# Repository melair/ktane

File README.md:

# Keep Talking and Nobody Explodes - Physical Version

## Version Two

This is version two of my Keep Talking and Nobody Explodes physical bomb, you may refer to the `version-one` branch if you wish to see the first version progress.

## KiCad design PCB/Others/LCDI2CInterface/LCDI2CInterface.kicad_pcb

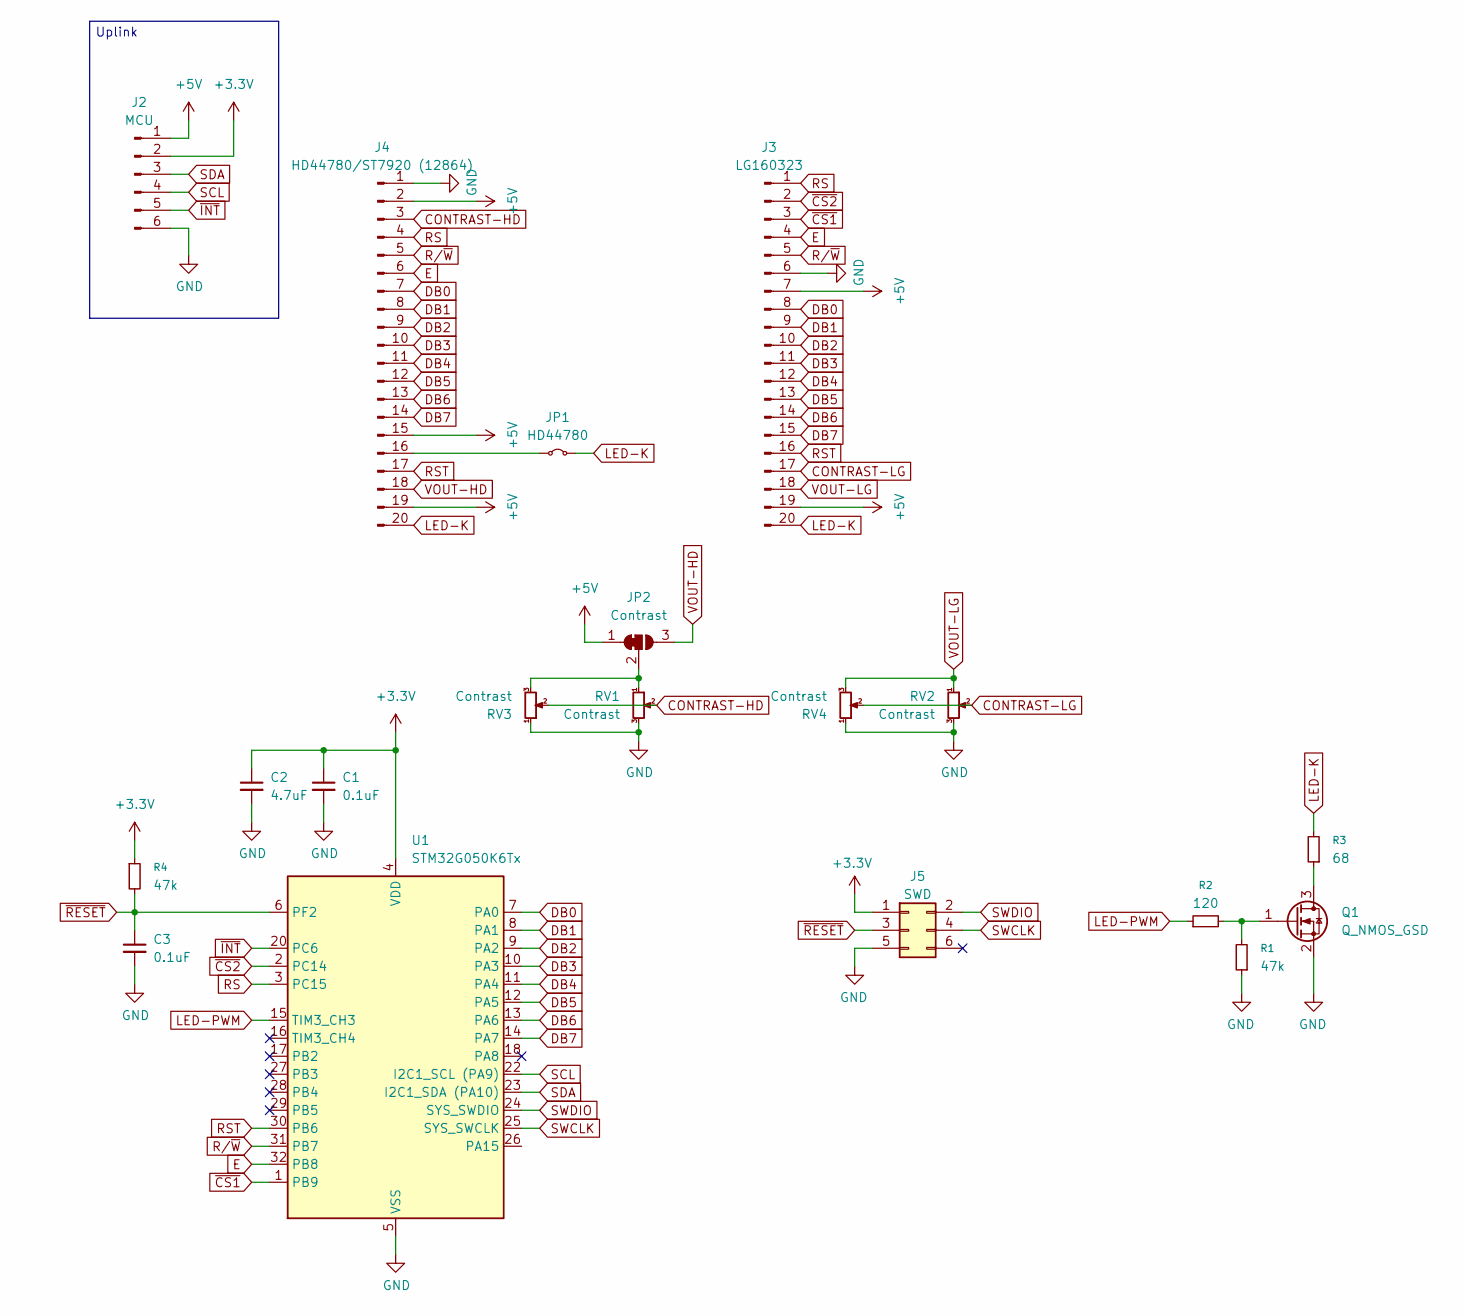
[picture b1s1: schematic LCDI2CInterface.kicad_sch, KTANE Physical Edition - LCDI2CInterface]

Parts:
C1, C3: 0.1uF; C_0603_1608Metric
C2: 4.7uF; C_0603_1608Metric
J2: MCU; PinHeader_1x06_P2.54mm_Horizontal
J3: LG160323; PinHeader_1x20_P2.54mm_Vertical
J4: HD44780/ST7920 (12864); PinHeader_1x20_P2.54mm_Vertical
J5: SWD; Tag-Connect_TC2030-IDC-NL_2x03_P1.27mm_Vertical; DIGIKEY NONE
JP1: HD44780; SolderJumper-2_P1.3mm_Bridged_RoundedPad1.0x1.5mm
JP2: Contrast; SolderJumper-3_P1.3mm_Bridged12_RoundedPad1.0x1.5mm
Q1: Q_NMOS_GSD; SOT-23
R1, R4: 47k; R_0603_1608Metric
R2: 120; R_0603_1608Metric
R3: 68; R_0603_1608Metric
RV1, RV2, RV3, RV4: Contrast; Potentiometer_Bourns_TC33X_Vertical; DIGIKEY TC33X-103ECT-ND
U1: STM32G050K6Tx; LQFP-32_7x7mm_P0.8mm

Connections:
+3.3V: C1.1, C2.1, J2.2, J5.1, R4.1, U1.4 (VDD)
+5V: J2.1, J3.7, J3.19, J4.2, J4.15, J4.19, JP2.1 (A)
CONTRAST-HD: J4.3, RV1.2, RV3.2
CONTRAST-LG: J3.17, RV2.2, RV4.2
DB0: J3.8, J4.7, U1.7 (PA0)
DB1: J3.9, J4.8, U1.8 (PA1)
DB2: J3.10, J4.9, U1.9 (PA2)
DB3: J3.11, J4.10, U1.10 (PA3)
DB4: J3.12, J4.11, U1.11 (PA4)
DB5: J3.13, J4.12, U1.12 (PA5)
DB6: J3.14, J4.13, U1.13 (PA6)
DB7: J3.15, J4.14, U1.14 (PA7)
E: J3.4, J4.6, U1.32 (PB8)
GND: C1.2, C2.2, C3.2, J2.6, J3.6, J4.1, J5.5, Q1.2 (S), R1.1, RV1.3, RV2.3, RV3.1, RV4.1, U1.5 (VSS)
LED-K: J3.20, J4.20, JP1.2 (B), R3.2
LED-PWM: R2.1, U1.15 (TIM3_CH3)
unnamed: J4.16, JP1.1 (A)
unnamed: JP2.2 (C), RV1.1, RV3.3
unnamed: Q1.3 (D), R3.1
unnamed: Q1.1 (G), R1.2, R2.2
RS: J3.1, J4.4, U1.3 (PC15)
RST: J3.16, J4.17, U1.30 (PB6)
R/~W: J3.5, J4.5, U1.31 (PB7)
SCL: J2.4, U1.22 (I2C1_SCL (PA9))
SDA: J2.3, U1.23 (I2C1_SDA (PA10))
SWCLK: J5.4, U1.25 (SYS_SWCLK)
SWDIO: J5.2, U1.24 (SYS_SWDIO)
VOUT-HD: J4.18, JP2.3 (B)
VOUT-LG: J3.18, RV2.1, RV4.3
~CS1: J3.3, U1.1 (PB9)
~CS2: J3.2, U1.2 (PC14)
~INT: J2.5, U1.20 (PC6)
~RESET: C3.1, J5.3, R4.2, U1.6 (PF2)

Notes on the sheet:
Uplink

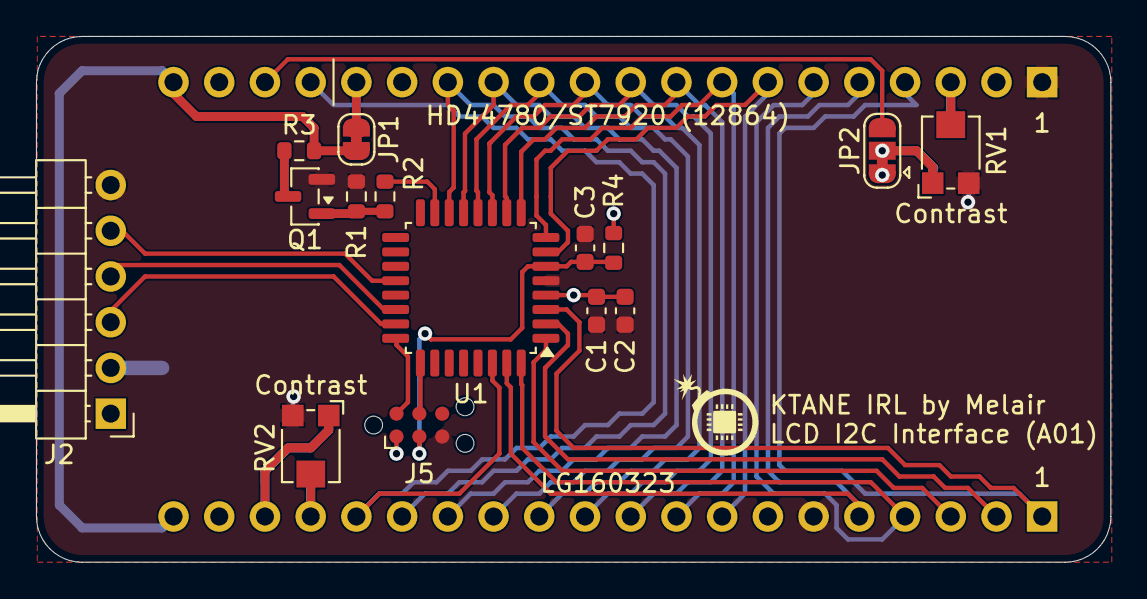
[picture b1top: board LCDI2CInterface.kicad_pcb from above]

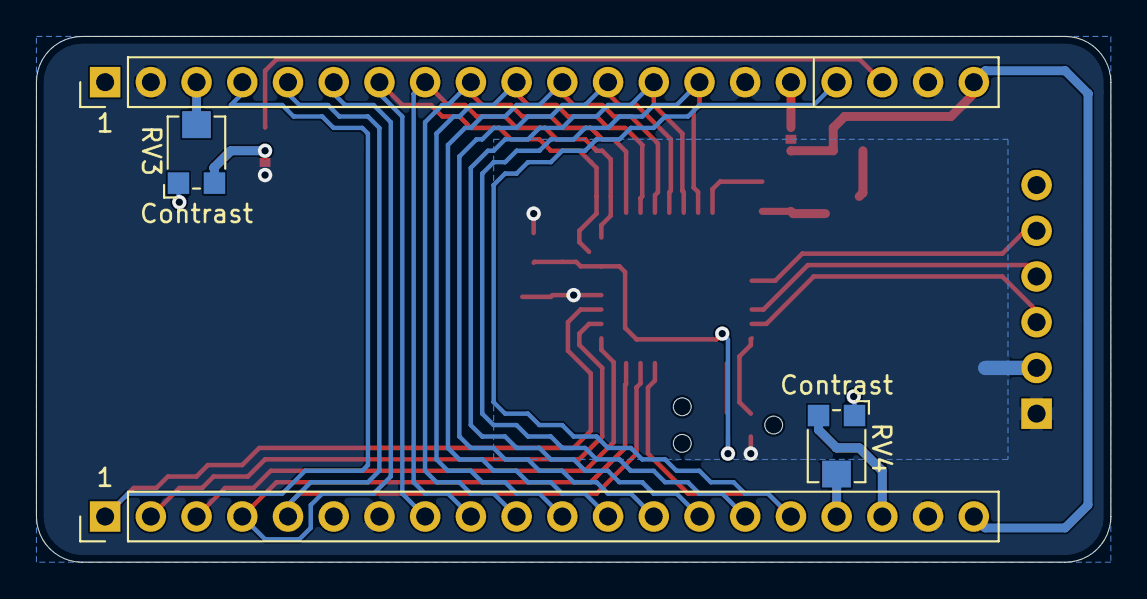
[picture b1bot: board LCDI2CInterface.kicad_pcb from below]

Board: 2 copper layers, 59.7 x 29.2 mm, 19 parts (4 on the bottom side), 33 nets.

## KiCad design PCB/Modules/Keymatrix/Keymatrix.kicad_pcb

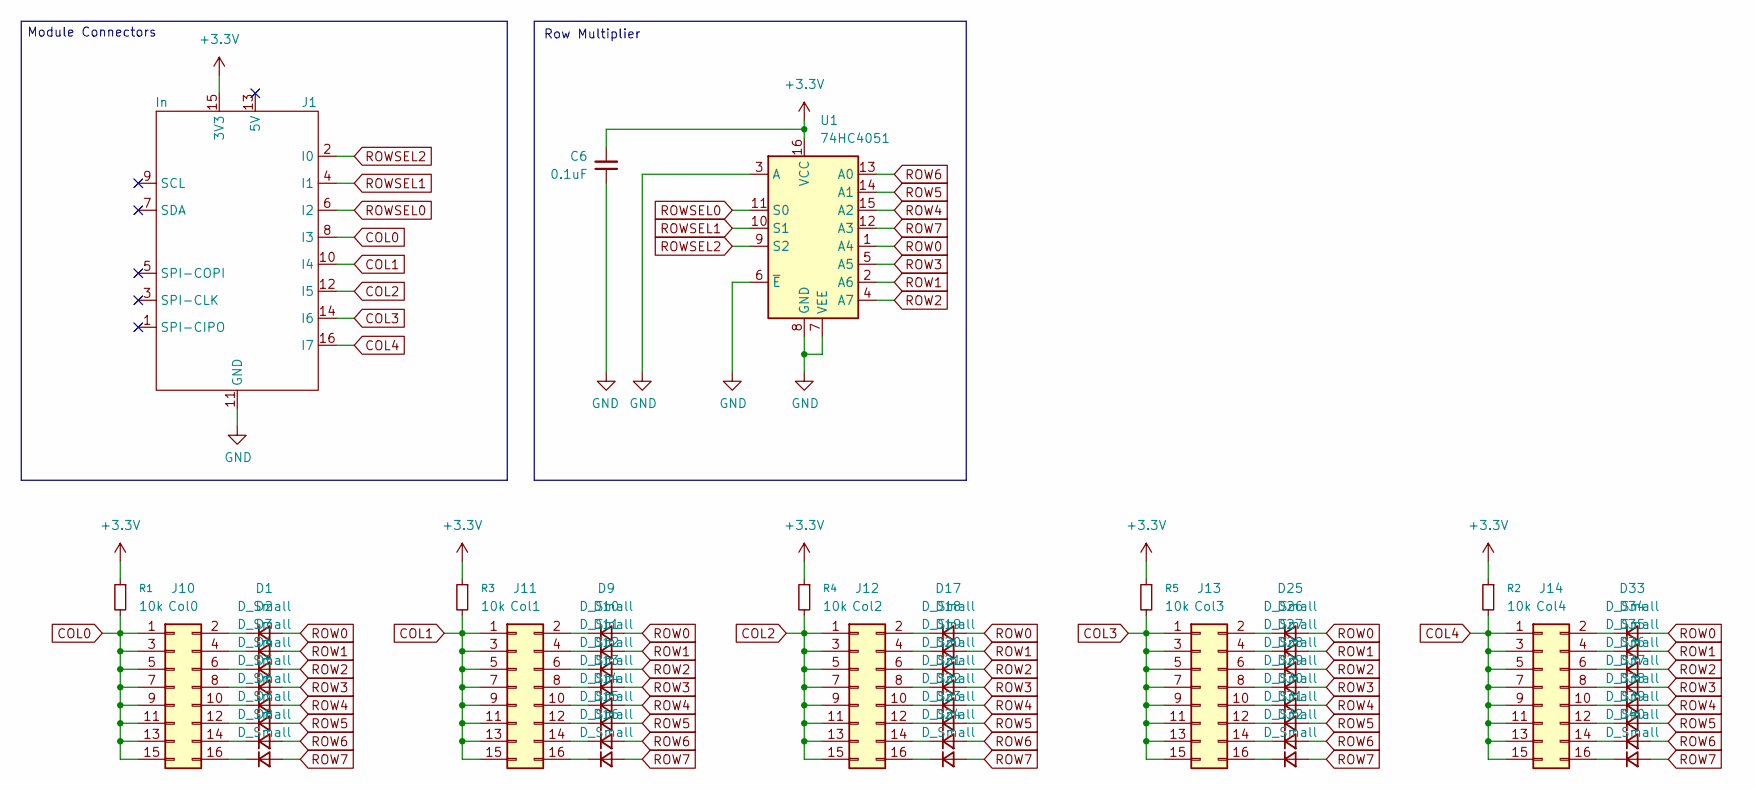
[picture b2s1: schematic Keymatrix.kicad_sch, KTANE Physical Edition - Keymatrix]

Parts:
C6: 0.1uF; C_0603_1608Metric
D1, D2, D3, D4, D5, D6, D7, D8, D9, D10, D11, D12, D13, D14, D15, D16, D17, D18, D19, D20, D21, D22, D23, D24, D25, D26, D27, D28, D29, D30, D31, D32, D33, D34, D35, D36, D37, D38, D39, D40: D_Small; D_0603_1608Metric
J1: In; KTANE Submodule Connector V2 - Short; DIGIKEY STOCK
J10: Col0; PinHeader_2x08_P2.54mm_Vertical
J11: Col1; PinHeader_2x08_P2.54mm_Vertical
J12: Col2; PinHeader_2x08_P2.54mm_Vertical
J13: Col3; PinHeader_2x08_P2.54mm_Vertical
J14: Col4; PinHeader_2x08_P2.54mm_Vertical
R1, R2, R3, R4, R5: 10k; R_0603_1608Metric
U1: 74HC4051; DHVQFN-16-1EP_2.5x3.5mm_P0.5mm_EP1x2mm

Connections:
+3.3V: C6.2, J1.15 (3V3), R1.1, R2.1, R3.1, R4.1, R5.1, U1.16 (VCC)
COL0: J1.8 (I3), J10.1, J10.3, J10.5, J10.7, J10.9, J10.11, J10.13, J10.15, R1.2
COL1: J1.10 (I4), J11.1, J11.3, J11.5, J11.7, J11.9, J11.11, J11.13, J11.15, R3.2
COL2: J1.12 (I5), J12.1, J12.3, J12.5, J12.7, J12.9, J12.11, J12.13, J12.15, R4.2
COL3: J1.14 (I6), J13.1, J13.3, J13.5, J13.7, J13.9, J13.11, J13.13, J13.15, R5.2
COL4: J1.16 (I7), J14.1, J14.3, J14.5, J14.7, J14.9, J14.11, J14.13, J14.15, R2.2
GND: C6.1, J1.11 (GND), U1.3 (A), U1.6 (~E), U1.7 (VEE), U1.8 (GND)
unnamed: D1.1 (K), J10.2
unnamed: D2.1 (K), J10.4
unnamed: D3.1 (K), J10.6
unnamed: D4.1 (K), J10.8
unnamed: D5.1 (K), J10.10
unnamed: D6.1 (K), J10.12
unnamed: D7.1 (K), J10.14
unnamed: D8.1 (K), J10.16
unnamed: D9.1 (K), J11.2
unnamed: D10.1 (K), J11.4
unnamed: D11.1 (K), J11.6
unnamed: D12.1 (K), J11.8
unnamed: D13.1 (K), J11.10
unnamed: D14.1 (K), J11.12
unnamed: D15.1 (K), J11.14
unnamed: D16.1 (K), J11.16
unnamed: D17.1 (K), J12.2
unnamed: D18.1 (K), J12.4
unnamed: D19.1 (K), J12.6
unnamed: D20.1 (K), J12.8
unnamed: D21.1 (K), J12.10
unnamed: D22.1 (K), J12.12
unnamed: D23.1 (K), J12.14
unnamed: D24.1 (K), J12.16
unnamed: D25.1 (K), J13.2
unnamed: D26.1 (K), J13.4
unnamed: D27.1 (K), J13.6
unnamed: D28.1 (K), J13.8
unnamed: D29.1 (K), J13.10
unnamed: D30.1 (K), J13.12
unnamed: D31.1 (K), J13.14
unnamed: D32.1 (K), J13.16
unnamed: D33.1 (K), J14.2
unnamed: D34.1 (K), J14.4
unnamed: D35.1 (K), J14.6
unnamed: D36.1 (K), J14.8
unnamed: D37.1 (K), J14.10
unnamed: D38.1 (K), J14.12
unnamed: D39.1 (K), J14.14
unnamed: D40.1 (K), J14.16
ROW0: D1.2 (A), D9.2 (A), D17.2 (A), D25.2 (A), D33.2 (A), U1.1 (A4)
ROW1: D2.2 (A), D10.2 (A), D18.2 (A), D26.2 (A), D34.2 (A), U1.2 (A6)
ROW2: D3.2 (A), D11.2 (A), D19.2 (A), D27.2 (A), D35.2 (A), U1.4 (A7)
ROW3: D4.2 (A), D12.2 (A), D20.2 (A), D28.2 (A), D36.2 (A), U1.5 (A5)
ROW4: D5.2 (A), D13.2 (A), D21.2 (A), D29.2 (A), D37.2 (A), U1.15 (A2)
ROW5: D6.2 (A), D14.2 (A), D22.2 (A), D30.2 (A), D38.2 (A), U1.14 (A1)
ROW6: D7.2 (A), D15.2 (A), D23.2 (A), D31.2 (A), D39.2 (A), U1.13 (A0)
ROW7: D8.2 (A), D16.2 (A), D24.2 (A), D32.2 (A), D40.2 (A), U1.12 (A3)
ROWSEL0: J1.6 (I2), U1.11 (S0)
ROWSEL1: J1.4 (I1), U1.10 (S1)
ROWSEL2: J1.2 (I0), U1.9 (S2)

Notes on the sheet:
Module Connectors
Row Multiplier

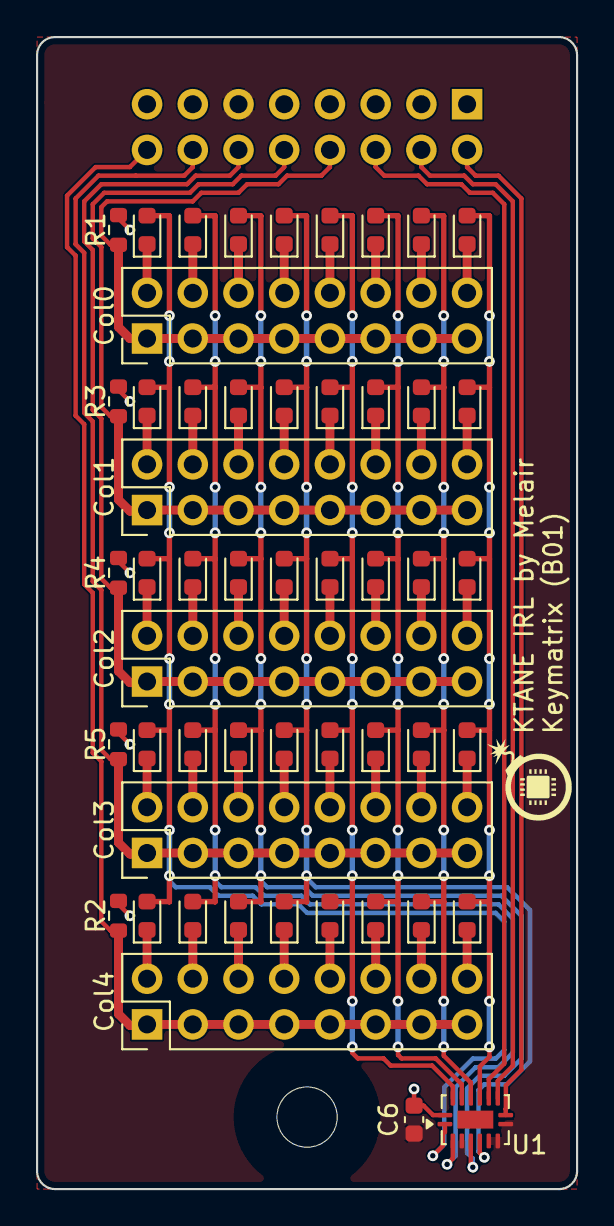
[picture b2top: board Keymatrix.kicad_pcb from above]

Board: 2 copper layers, 30.0 x 64.0 mm, 53 parts (0 on the bottom side), 58 nets.

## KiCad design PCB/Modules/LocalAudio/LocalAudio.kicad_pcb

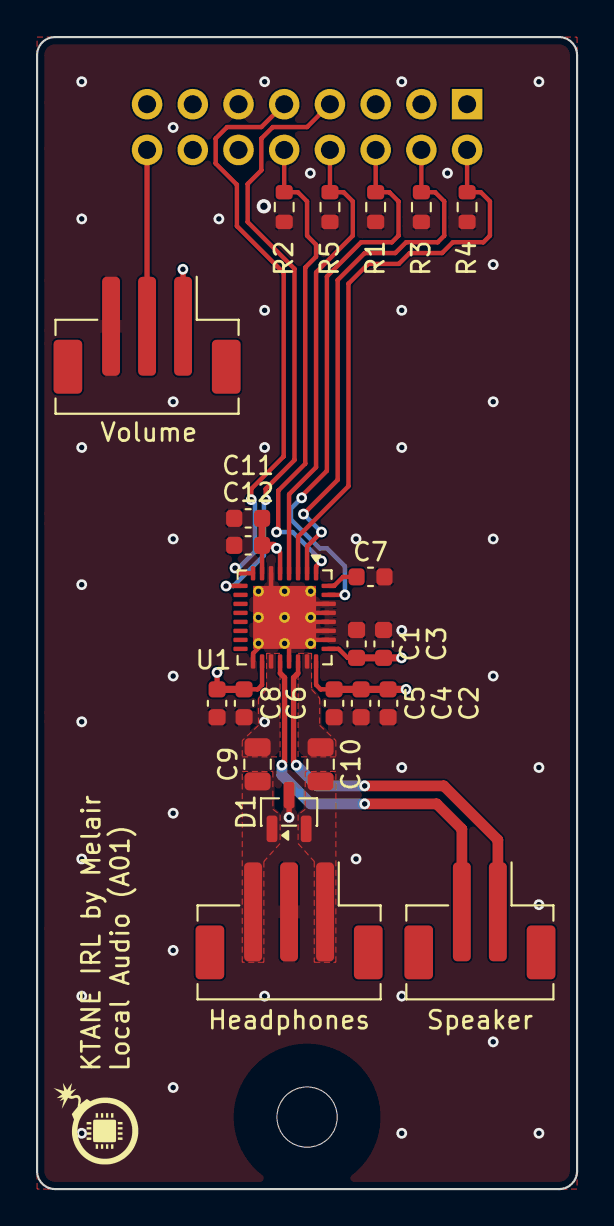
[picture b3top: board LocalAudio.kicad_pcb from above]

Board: 4 copper layers, 30.0 x 64.0 mm, 23 parts (0 on the bottom side), 17 nets.

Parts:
C1, C5, C6, C7, C12: 0.1uF; C_0603_1608Metric
C2: 10uF; C_0603_1608Metric
C3, C4, C8, C11: 1uF; C_0603_1608Metric
C9, C10: 47uF; C_0805_2012Metric
D1: PESD3V3S2BT; SOT-23
J1: In; KTANE Submodule Connector V2 - Short
J2: Speaker; JST_PH_B2B-PH-SM4-TB_1x02-1MP_P2.00mm_Vertical
J3: Headphones; JST_PH_B3B-PH-SM4-TB_1x03-1MP_P2.00mm_Vertical
J4: Volume; JST_PH_B3B-PH-SM4-TB_1x03-1MP_P2.00mm_Vertical
R1, R2, R3, R4, R5: 4.7k; R_0603_1608Metric
U1: TLV320DAC32; VQFN-32-1EP_5x5mm_P0.5mm_EP3.5x3.5mm_ThermalVias

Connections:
+3.3V: C1.2, C2.2, C3.2, C4.2, C5.2, C6.2, C8.2, C11.2, C12.2, J1.15 (3V3), J4.1, U1.5 (LDO_SELECT), U1.7 (IOVDD), U1.18 (DRVDD), U1.24 (DRVDD), U1.25 (AVDD_DAC)
GND: C1.1, C2.1, C3.1, C4.1, C5.1, C6.1, C7.1, C8.1, C11.1, C12.1, D1.3 (CC), J1.11 (GND), J3.2, J4.3, R1.1, R2.1, R3.1, R4.1, R5.1, U1.6 (IOVSS), U1.17 (DRVSS), U1.21 (DRVSS), U1.26 (VSS_DAC), U1.27 (VSS_DAC), U1.28 (VSS_DAC), U1.29 (VSS_DAC), U1.30 (VSS_DAC), U1.33 (VSS_DAC)
I2C-CLK: J1.9 (SCL), U1.8 (SCL)
I2C-DAT: J1.7 (SDA), U1.9 (SDA)
I2S-BCLK: J1.4 (I2S_CK), R3.2, U1.2 (BCLK)
I2S-DAT: J1.8 (I2S_SDO), R5.2, U1.4 (DIN)
I2S-MCLK: J1.10 (I2S_MCLK), R2.2, U1.1 (MCLK)
I2S-WCLK: J1.2 (I2S_WS), R4.2, U1.3 (WCLK)
unnamed: C9.2, D1.1 (K1), J3.3
unnamed: C10.2, D1.2 (K2), J3.1
unnamed: C7.2, U1.32 (DVDD)
unnamed: C9.1, U1.19 (HPLOUT)
unnamed: C10.1, U1.23 (HPROUT)
SPK+: J2.1, U1.22 (HPRCOM)
SPK-: J2.2, U1.20 (HPLCOM)
VOL: J1.16 (I7), J4.2
~RESET: J1.6 (I2S_SDI), R1.2, U1.31 (~RESET)

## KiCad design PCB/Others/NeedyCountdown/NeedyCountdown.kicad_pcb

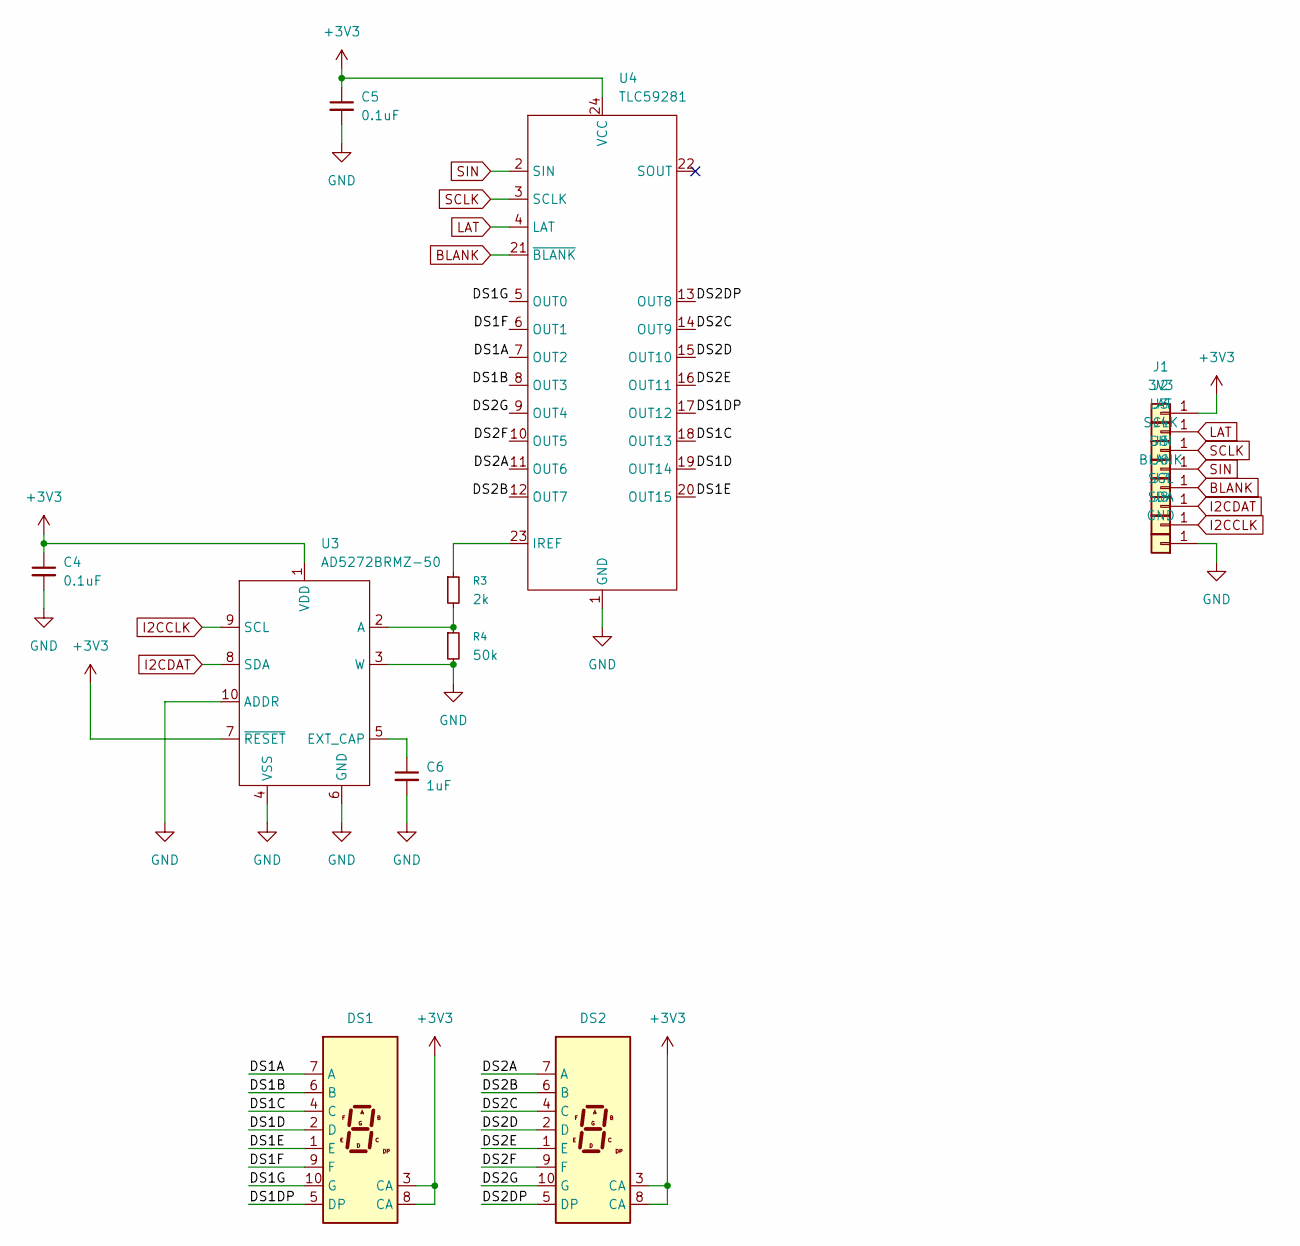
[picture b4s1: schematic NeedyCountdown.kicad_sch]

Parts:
C4, C5: 0.1uF; C_0603_1608Metric; DIGIKEY 1276-1005-1-ND
C6: 1uF; C_0603_1608Metric; DIGIKEY 1276-1946-1-ND
DS1, DS2: 5161 LED
J1: 3V3; Pad4x2; DIGIKEY NONE
J2: LAT; Pad4x2; DIGIKEY NONE
J3: SCLK; Pad4x2; DIGIKEY NONE
J4: SIN; Pad4x2; DIGIKEY NONE
J5: BLANK; Pad4x2; DIGIKEY NONE
J6: SCL; Pad4x2; DIGIKEY NONE
J7: SDA; Pad4x2; DIGIKEY NONE
J8: GND; Pad4x2; DIGIKEY NONE
R3: 2k; R_0603_1608Metric; DIGIKEY P2.00KHCT-ND
R4: 50k; R_0603_1608Metric; DIGIKEY P51.0KHCT-ND
U3: AD5272BRMZ-50; MSOP-10_3x3mm_P0.5mm; DIGIKEY 505-AD5272BRMZ-50-ND
U4: TLC59281; SSOP-24_3.9x8.7mm_P0.635mm; DIGIKEY 296-25789-1-ND

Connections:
+3V3: C4.1, C5.1, DS1.3 (CA), DS1.8 (CA), DS2.3 (CA), DS2.8 (CA), J1.1 (Pin_1_1), U3.1 (VDD), U3.7 (~RESET), U4.24 (VCC)
/DS1A: DS1.7 (A), U4.7 (OUT2)
/DS1B: DS1.6 (B), U4.8 (OUT3)
/DS1C: DS1.4 (C), U4.18 (OUT13)
/DS1D: DS1.2 (D), U4.19 (OUT14)
/DS1DP: DS1.5 (DP), U4.17 (OUT12)
/DS1E: DS1.1 (E), U4.20 (OUT15)
/DS1F: DS1.9 (F), U4.6 (OUT1)
/DS1G: DS1.10 (G), U4.5 (OUT0)
/DS2A: DS2.7 (A), U4.11 (OUT6)
/DS2B: DS2.6 (B), U4.12 (OUT7)
/DS2C: DS2.4 (C), U4.14 (OUT9)
/DS2D: DS2.2 (D), U4.15 (OUT10)
/DS2DP: DS2.5 (DP), U4.13 (OUT8)
/DS2E: DS2.1 (E), U4.16 (OUT11)
/DS2F: DS2.9 (F), U4.10 (OUT5)
/DS2G: DS2.10 (G), U4.9 (OUT4)
BLANK: J5.1 (Pin_1_1), U4.21 (~BLANK)
GND: C4.2, C5.2, C6.2, J8.1 (Pin_1_1), R4.2, U3.3 (W), U3.4 (VSS), U3.6 (GND), U3.10 (ADDR), U4.1 (GND)
I2CCLK: J7.1 (Pin_1_1), U3.9 (SCL)
I2CDAT: J6.1 (Pin_1_1), U3.8 (SDA)
LAT: J2.1 (Pin_1_1), U4.4 (LAT)
unnamed: R3.2, R4.1, U3.2 (A)
unnamed: C6.1, U3.5 (EXT_CAP)
unnamed: R3.1, U4.23 (IREF)
SCLK: J3.1 (Pin_1_1), U4.3 (SCLK)
SIN: J4.1 (Pin_1_1), U4.2 (SIN)

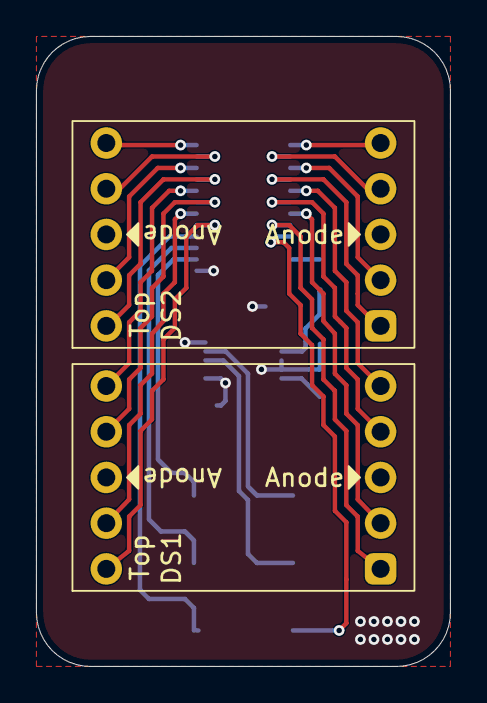
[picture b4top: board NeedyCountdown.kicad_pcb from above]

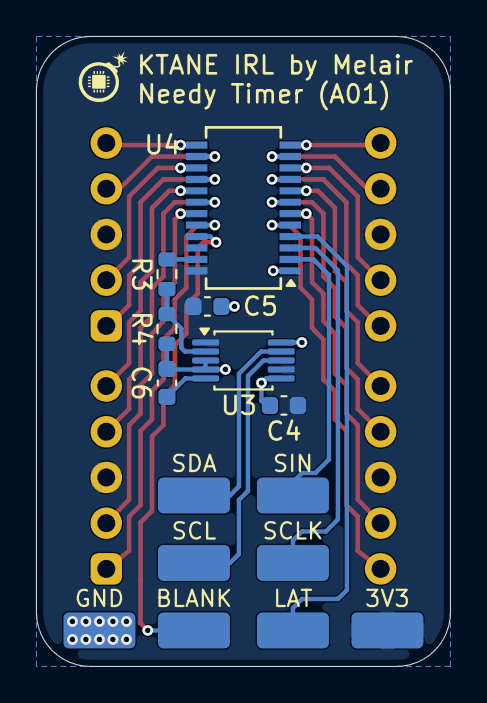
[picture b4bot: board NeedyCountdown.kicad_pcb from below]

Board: 2 copper layers, 23.0 x 35.0 mm, 17 parts (15 on the bottom side), 27 nets.

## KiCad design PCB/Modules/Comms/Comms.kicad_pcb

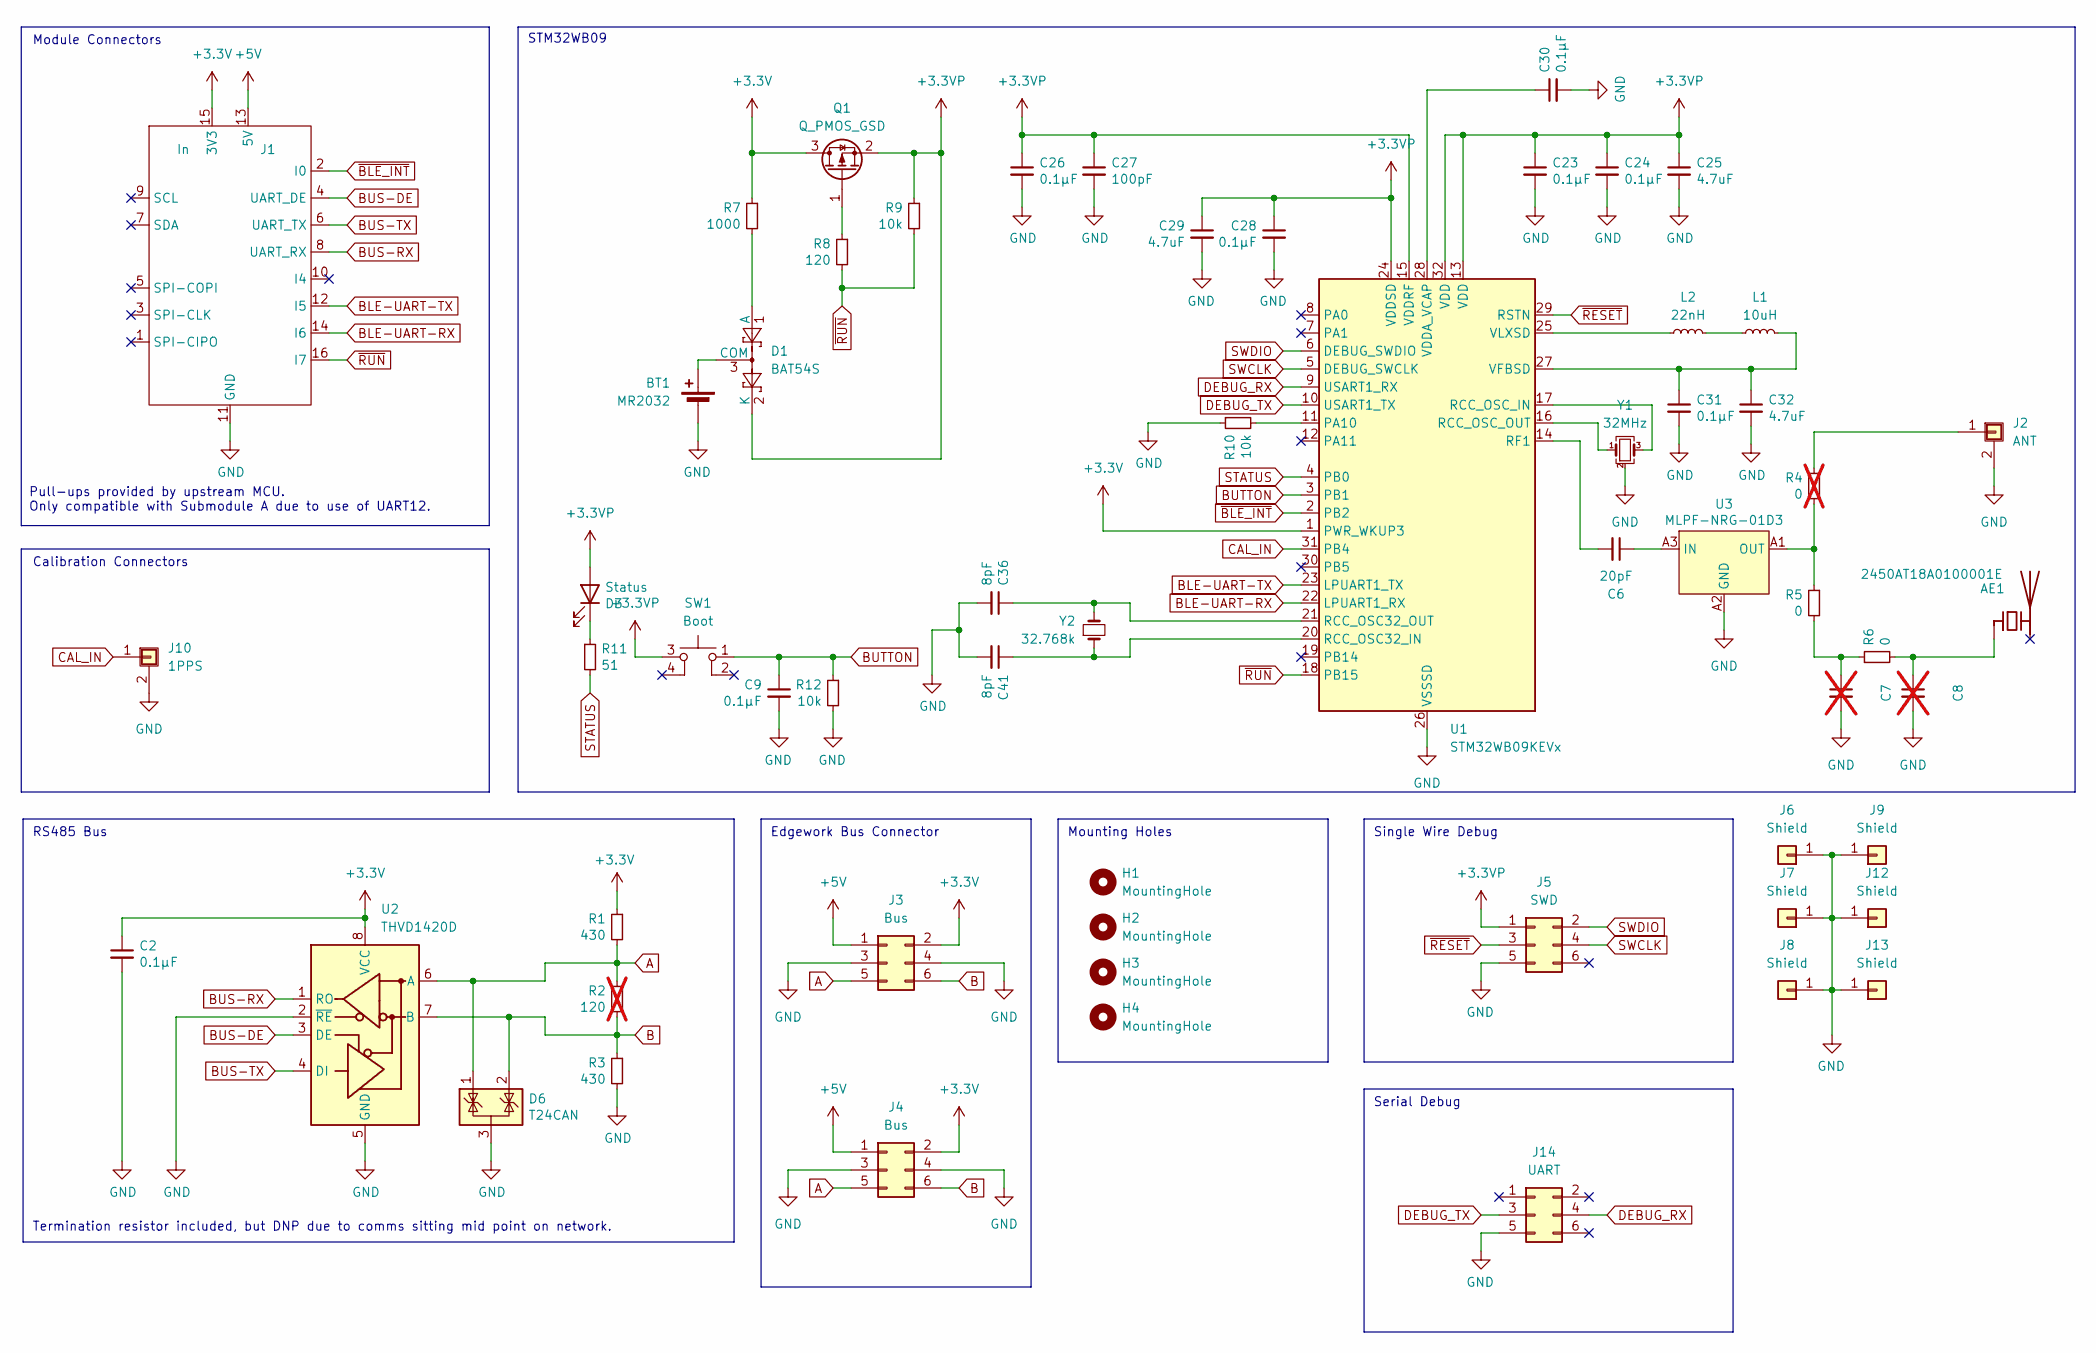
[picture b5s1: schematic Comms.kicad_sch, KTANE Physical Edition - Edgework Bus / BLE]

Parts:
AE1: 2450AT18A0100001E; Johanson_2450AT18x100_2400-2500Mhz; DIGIKEY 712-2450AT18A0100001ECT-ND
BT1: MR2032; CellHolder
C2, C9, C23, C24, C26, C28, C30, C31: 0.1μF; C_0603_1608Metric; DIGIKEY 1276-1005-1-ND
C6: 20pF; R_0402_1005Metric_Tweaked; DIGIKEY 1276-6601-1-ND
C7, C8: R_0402_1005Metric_Tweaked; DIGIKEY NONE; not fitted
C25, C29, C32: 4.7uF; C_0603_1608Metric; DIGIKEY 1276-2087-1-ND
C27: 100pF; C_0603_1608Metric; DIGIKEY 1276-1005-1-ND
C36, C41: 8pF; C_0603_1608Metric; DIGIKEY 490-GCM1885C2A8R0BA16JCT-ND
D1: BAT54S; SOT-23; DIGIKEY BAT54SLT1GOSCT-ND
D3: Status; LED_0603_1608Metric; DIGIKEY 160-1827-1-ND
D6: T24CAN; SOT-23; DIGIKEY STOCK
H1, H2, H3, H4: MountingHole; MountingHole_3.2mm_M3_NoCopper; DIGIKEY NONE
J1: In; PinHeader_2x08_P2.54mm_Vertical-Centered; DIGIKEY S9171-ND
J2: ANT; U.FL_Hirose_U.FL-R-SMT-1_Vertical; DIGIKEY 26-U.FL-R-SMT-1(32)CT-ND
J3, J4: Bus; PinHeader_2x03_P2.54mm_Vertical-Centered; DIGIKEY S9716-ND
J5: SWD; Tag-Connect_TC2030-IDC-NL_2x03_P1.27mm_Vertical; DIGIKEY NONE
J6, J7, J8, J9: Shield; EMI_Shield_Corner; DIGIKEY STOCK/AliExpress
J10: 1PPS; U.FL_Hirose_U.FL-R-SMT-1_Vertical; DIGIKEY 26-U.FL-R-SMT-1(32)CT-ND
J12, J13: Shield; EMI_Shield_Straight; DIGIKEY STOCK/AliExpress
J14: UART; Tag-Connect_TC2030-IDC-NL_2x03_P1.27mm_Vertical; DIGIKEY NONE
L1: 10uH; L_0805_2012Metric; DIGIKEY 490-LQM21DN100M70LCT-ND
L2: 22nH; L_0402_1005Metric; DIGIKEY 490-LQG15HN22NG02DCT-ND
Q1: Q_PMOS_GSD; SOT-23; DIGIKEY 4518-SI2307ACT-ND
R1, R3: 430; R_0603_1608Metric; DIGIKEY P430HCT-ND
R2: 120; R_0603_1608Metric; DIGIKEY P120HCT-ND; not fitted
R4: 0; R_0402_1005Metric_Tweaked; DIGIKEY 10-ERJ-H2G0R00XCT-ND; not fitted
R5, R6: 0; R_0402_1005Metric_Tweaked; DIGIKEY 10-ERJ-H2G0R00XCT-ND
R7: 1000; R_0603_1608Metric; DIGIKEY P1.00KHCT-ND
R8: 120; R_0603_1608Metric; DIGIKEY P120HCT-ND
R9, R10, R12: 10k; R_0603_1608Metric; DIGIKEY P10.0KHCT-ND
R11: 51; R_0603_1608Metric; DIGIKEY P51.0HCT-ND
SW1: Boot; PTS526Sx15SMTR2xLFS; DIGIKEY CKN12220-1-ND
U1: STM32WB09KEVx; QFN-32-1EP_5x5mm_P0.5mm_EP3.7x3.7mm; DIGIKEY 497-STM32WB09KEV6TRCT-ND
U2: THVD1420D; SOT-583-8; DIGIKEY 296-THVD1420DRLRCT-ND
U3: MLPF-NRG-01D3; DIGIKEY 497-MLPF-NRG-01D3CT-ND
Y1: 32MHz; Crystal_SMD_2016-4Pin_2.0x1.6mm; DIGIKEY 644-CS06654-32MCT-ND
Y2: 32.768k; Crystal_SMD_2012-2Pin_2.0x1.2mm; DIGIKEY XC3096CT-ND

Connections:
+3.3V: C2.1, J1.15 (3V3), J3.2, J4.2, Q1.3 (D), R1.1, R7.1, U1.1 (PWR_WKUP3), U2.8 (VCC)
+3.3VP: C23.1, C24.1, C25.1, C26.1, C27.1, C28.1, C29.1, D1.2 (K), D3.2 (A), J5.1, Q1.2 (S), R9.1, SW1.3, U1.13 (VDD), U1.15 (VDDRF), U1.24 (VDDSD), U1.32 (VDD)
+5V: J1.13 (5V), J3.1, J4.1
A: D6.1 (K), J3.5, J4.5, R1.2, R2.1, U2.6 (A)
B: D6.2 (K), J3.6, J4.6, R2.2, R3.1, U2.7 (B)
BLE-UART-RX: J1.14 (I6), U1.22 (LPUART1_RX)
BLE-UART-TX: J1.12 (I5), U1.23 (LPUART1_TX)
BUS-DE: J1.4 (UART_DE), U2.3 (DE)
BUS-RX: J1.8 (UART_RX), U2.1 (RO)
BUS-TX: J1.6 (UART_TX), U2.4 (DI)
BUTTON: C9.1, R12.1, SW1.1, U1.3 (PB1)
CAL_IN: J10.1, U1.31 (PB4)
DEBUG_RX: J14.4, U1.9 (USART1_RX)
DEBUG_TX: J14.3, U1.10 (USART1_TX)
GND: BT1.2 (-), C2.2, C7.2, C8.2, C9.2, C23.2, C24.2, C25.2, C26.2, C27.2, C28.2, C29.2, C30.2, C31.2, C32.2, C36.2, C41.2, D6.3 (A), J1.11 (GND), J2.2 (Shield), J3.3, J3.4, J4.3, J4.4, J5.5, J6.1 (Pin_1_1), J7.1 (Pin_1_1), J8.1 (Pin_1_1), J9.1 (Pin_1_1), J10.2 (Shield), J12.1 (Pin_1_1), J13.1 (Pin_1_1), J14.5, R3.2, R10.1, R12.2, U1.26 (VSSSD), U1.33 (VSSSD), U2.2 (~RE), U2.5 (GND), U3.A2 (GND), U3.B1 (GND), U3.B2 (GND), U3.B3 (GND), Y1.2 (G), Y1.4 (G)
unnamed: AE1.1 (FEED_1), C8.1, R6.2
unnamed: BT1.1 (+), D1.3 (COM)
unnamed: C7.1, R5.2, R6.1
unnamed: D1.1 (A), R7.2
unnamed: D3.1 (K), R11.1
unnamed: J2.1, R4.1
unnamed: L1.2, L2.1
unnamed: Q1.1 (G), R8.1
unnamed: U1.17 (RCC_OSC_IN), Y1.3
unnamed: U1.16 (RCC_OSC_OUT), Y1.1
unnamed: R10.2, U1.11 (PA10)
unnamed: C36.1, U1.21 (RCC_OSC32_OUT), Y2.2
unnamed: C41.1, U1.20 (RCC_OSC32_IN), Y2.1
unnamed: C6.2, U1.14 (RF1)
unnamed: C30.1, U1.28 (VDDA_VCAP)
unnamed: C31.1, C32.1, L1.1, U1.27 (VFBSD)
unnamed: L2.2, U1.25 (VLXSD)
unnamed: C6.1, U3.A3 (IN)
unnamed: R4.2, R5.1, U3.A1 (OUT)
STATUS: R11.2, U1.4 (PB0)
SWCLK: J5.4, U1.5 (DEBUG_SWCLK)
SWDIO: J5.2, U1.6 (DEBUG_SWDIO)
~BLE_INT: J1.2 (I0), U1.2 (PB2)
~RESET: J5.3, U1.29 (RSTN)
~RUN: J1.16 (I7), R8.2, R9.2, U1.18 (PB15)

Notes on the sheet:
Pull-ups provided by upstream MCU. Only compatible with Submodule A due to use of UART12.
Single Wire Debug
RS485 Bus
Module Connectors
Termination resistor included, but DNP due to comms sitting mid point on network.
Serial Debug
Mounting Holes
STM32WB09
Calibration Connectors
Edgework Bus Connector

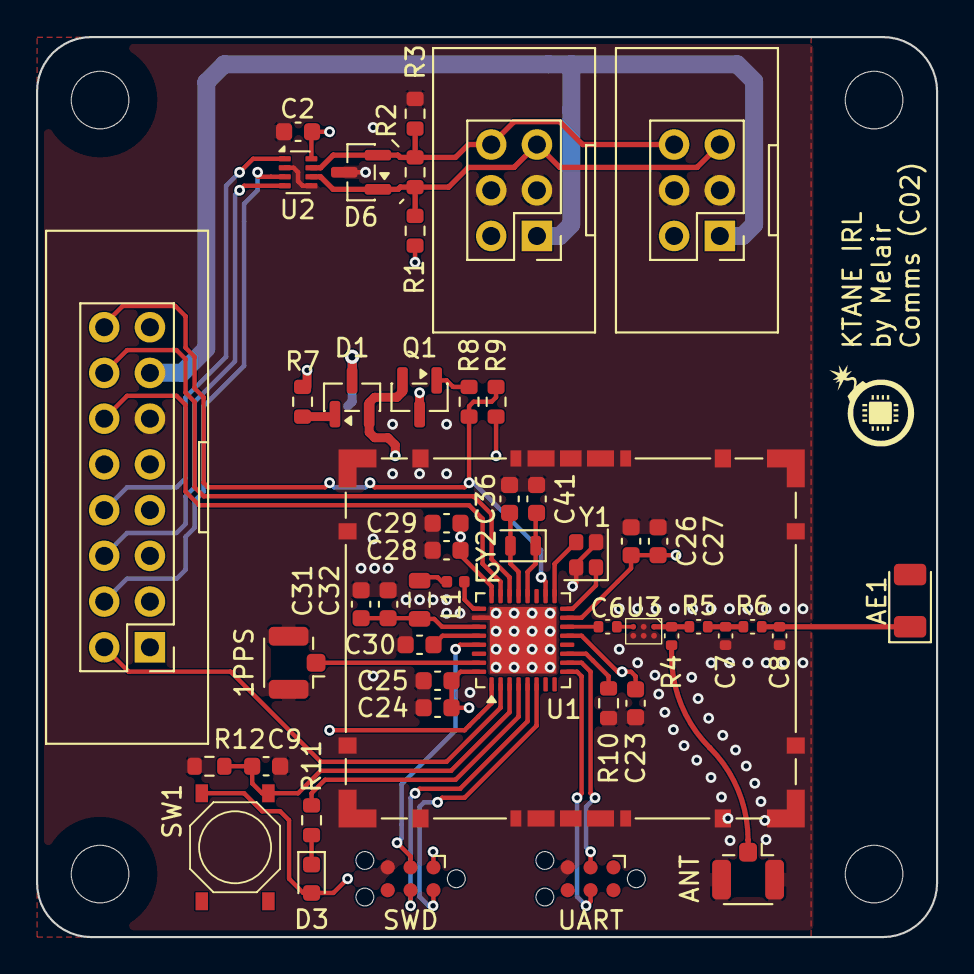
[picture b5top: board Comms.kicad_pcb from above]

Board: 4 copper layers, 50.0 x 50.0 mm, 60 parts (1 on the bottom side), 40 nets.

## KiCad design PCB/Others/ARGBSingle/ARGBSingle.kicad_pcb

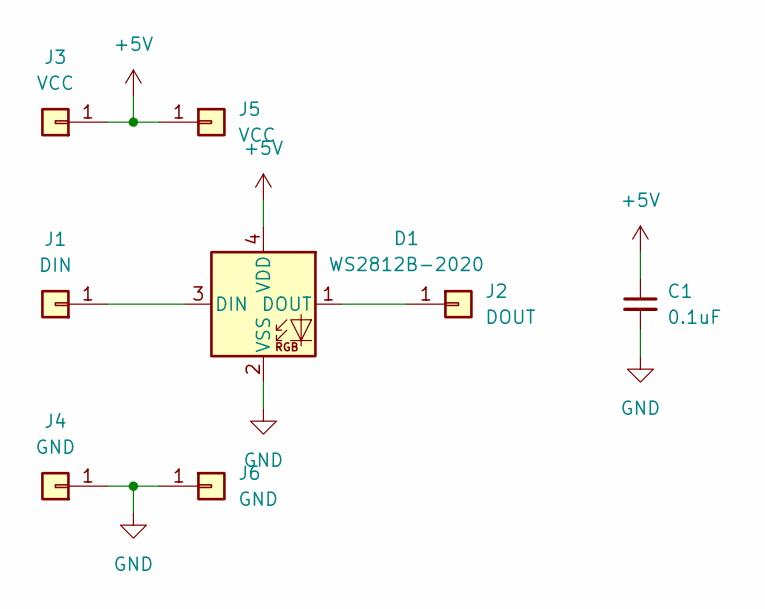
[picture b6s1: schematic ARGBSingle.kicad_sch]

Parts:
C1: 0.1uF; C_0603_1608Metric; JLCPCB Part # C597251
D1: WS2812B-2020; LED_WS2812B-2020_PLCC4_2.0x2.0mm; JLCPCB Part # C52917434
J1: DIN; Pad2.5x1.25
J2: DOUT; Pad2.5x1.25
J3, J5: VCC; Pad2.5x1.25
J4, J6: GND; Pad2.5x1.25

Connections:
+5V: C1.1, D1.4 (VDD), J3.1 (Pin_1_1), J5.1 (Pin_1_1)
GND: C1.2, D1.2 (VSS), J4.1 (Pin_1_1), J6.1 (Pin_1_1)
unnamed: D1.3 (DIN), J1.1 (Pin_1_1)
unnamed: D1.1 (DOUT), J2.1 (Pin_1_1)

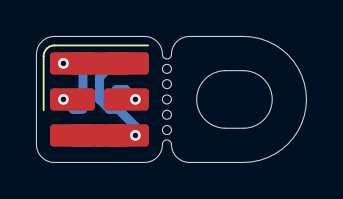
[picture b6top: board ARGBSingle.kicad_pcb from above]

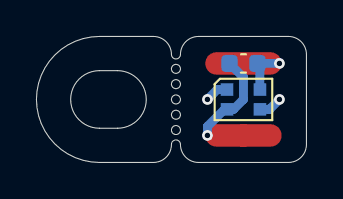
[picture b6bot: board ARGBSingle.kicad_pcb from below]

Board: 2 copper layers, 15.0 x 7.0 mm, 8 parts (2 on the bottom side), 4 nets.
